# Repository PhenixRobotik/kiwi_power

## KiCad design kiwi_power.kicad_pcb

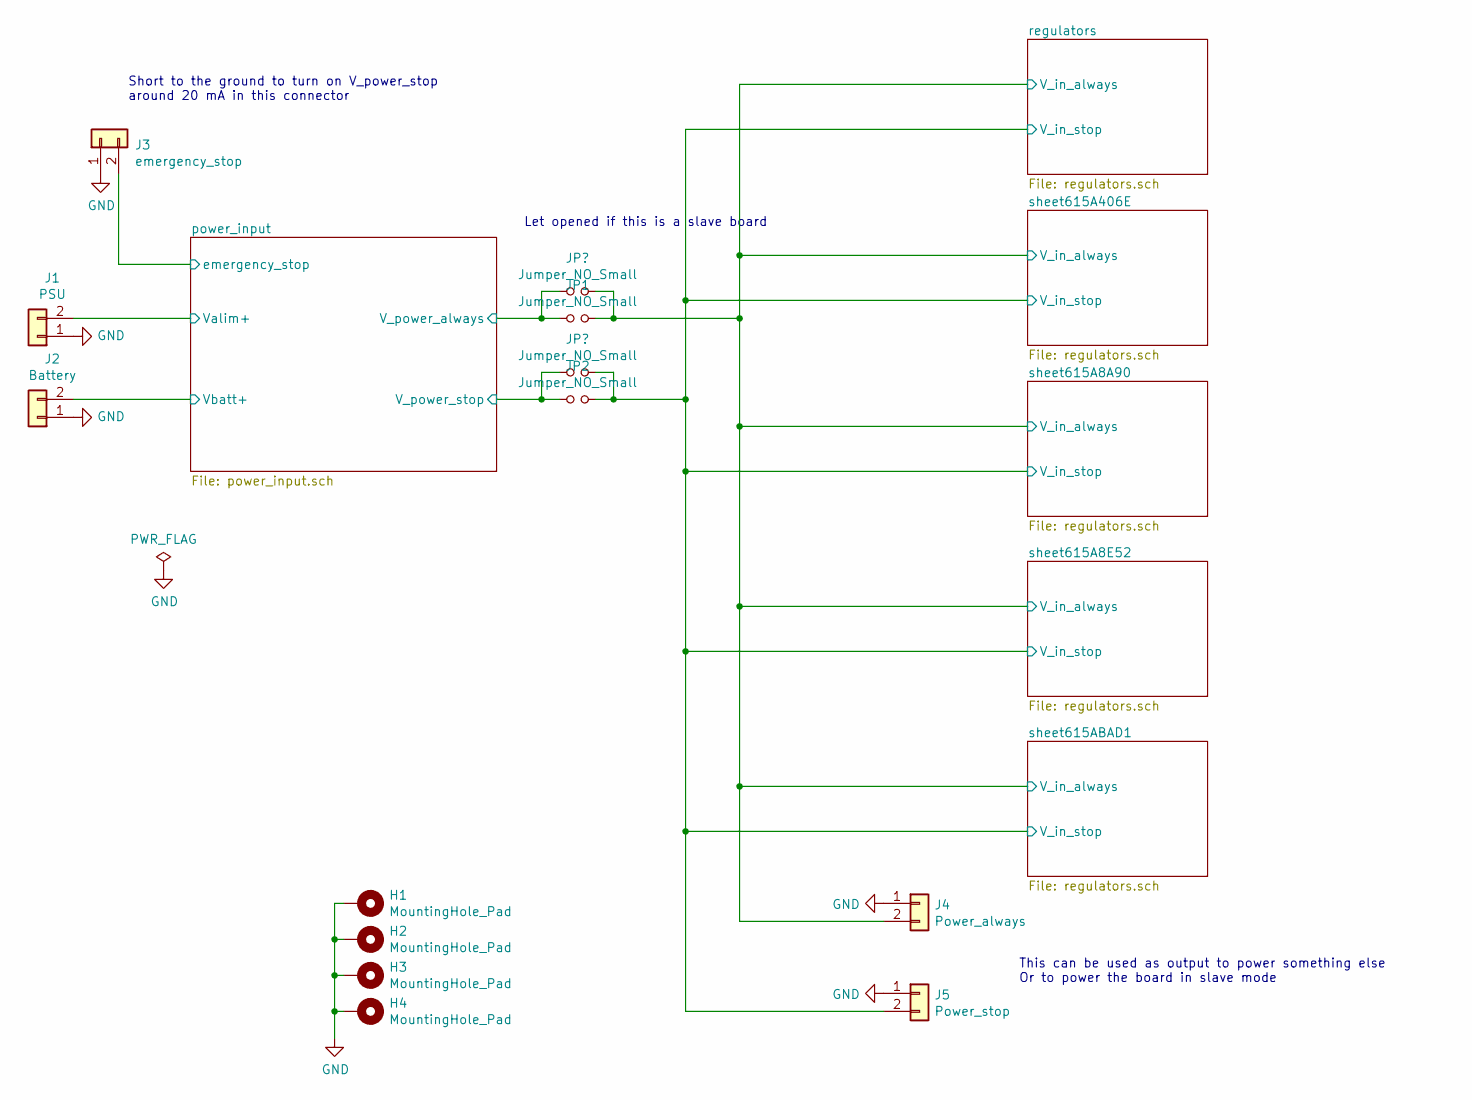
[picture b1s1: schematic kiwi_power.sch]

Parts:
H1, H2, H3, H4: MountingHole_Pad; MountingHole_3.2mm_M3_DIN965_Pad
J1: PSU; PhoenixContact_MSTBA_2,5_2-G-5,08_1x02_P5.08mm_Horizontal
J2: Battery; PhoenixContact_MSTBA_2,5_2-G-5,08_1x02_P5.08mm_Horizontal
J3: emergency_stop; JST_PH_S2B-PH-K_1x02_P2.00mm_Horizontal
J4: Power_always; PhoenixContact_MC_1,5_2-G-3.81_1x02_P3.81mm_Horizontal
J5: Power_stop; PhoenixContact_MC_1,5_2-G-3.81_1x02_P3.81mm_Horizontal
JP1, JP2: Jumper_NO_Small; PinHeader_1x02_P2.54mm_Vertical

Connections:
/power_input/V_power_always: JP1.1; also elsewhere on the board
/power_input/V_power_stop: JP2.1; also elsewhere on the board
/power_input/Valim+: J1.2; also elsewhere on the board
/power_input/Vbatt+: J2.2; also elsewhere on the board
/power_input/emergency_stop: J3.2; also elsewhere on the board
/regulators/V_in_always: J4.2, JP1.2; also elsewhere on the board
/regulators/V_in_stop: J5.2, JP2.2; also elsewhere on the board
GND: H1.1, H2.1, H3.1, H4.1, J1.1, J2.1, J3.1, J4.1, J5.1; also elsewhere on the board

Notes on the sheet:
Short to the ground to turn on V_power_stop around 20 mA in this connector
Let opened if this is a slave board
This can be used as output to power something else Or to power the board in slave mode

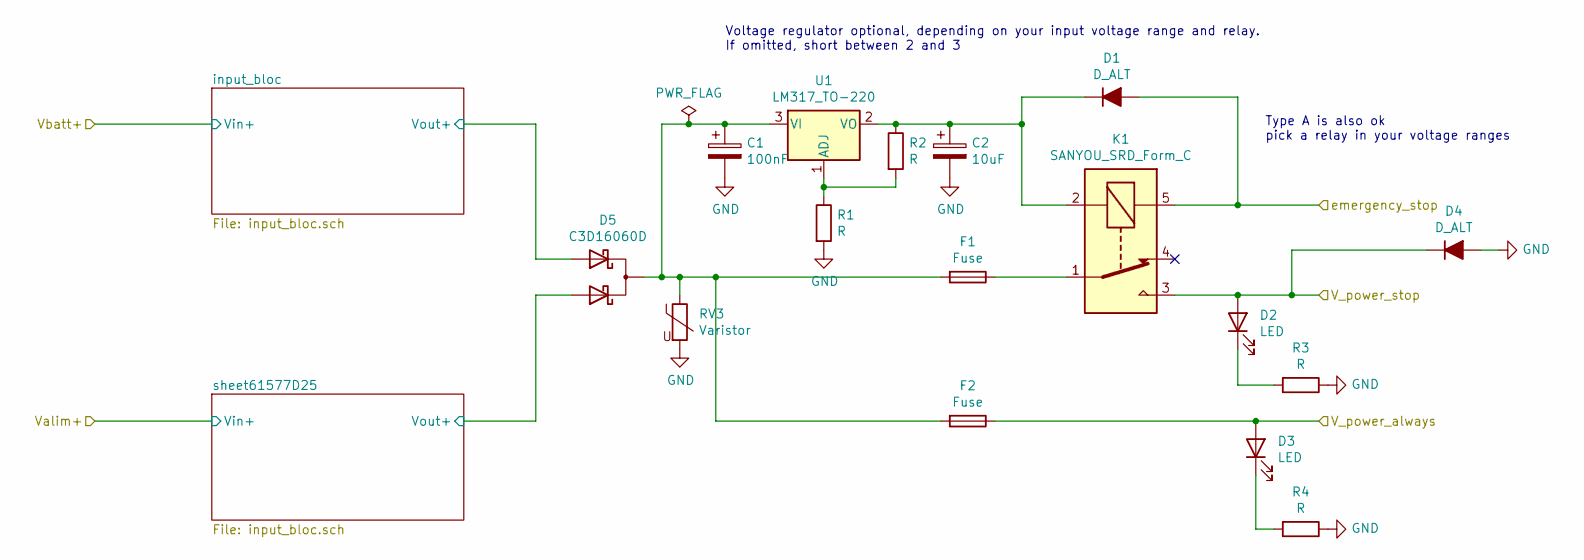
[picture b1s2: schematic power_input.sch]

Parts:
C1: 100nF; CP_Radial_D5.0mm_P2.00mm
C2: 10uF; CP_Radial_D5.0mm_P2.00mm
D1, D4: D_ALT; D_DO-35_SOD27_P10.16mm_Horizontal
D2, D3: LED; LED_D5.0mm
D5: C3D16060D; TO-220-3_Vertical
F1, F2: Fuse; Fuse_Littelfuse_372_D8.50mm
K1: SANYOU_SRD_Form_C; Relay_SPDT_SANYOU_SRD_Series_Form_C
R1, R2, R3, R4: R; R_Axial_DIN0207_L6.3mm_D2.5mm_P10.16mm_Horizontal
RV3: Varistor; RV_Disc_D7mm_W4mm_P5mm
U1: LM317_TO-220; TO-220-3_Vertical

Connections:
/power_input/V_power_always: D3.2 (A), F2.1; also elsewhere on the board
/power_input/V_power_stop: D2.2 (A), D4.1 (K), K1.3; also elsewhere on the board
/power_input/emergency_stop: D1.2 (A), K1.5; also elsewhere on the board
/power_input/input_bloc/Vout+: D5.1 (A1); also elsewhere on the board
/power_input/sheet61577D25/Vout+: D5.3 (A2); also elsewhere on the board
GND: C1.2, C2.2, D4.2 (A), R1.2, R3.1, R4.1, RV3.2; also elsewhere on the board
unnamed: C1.1, D5.2 (K), F1.2, F2.2, RV3.1, U1.3 (VI)
unnamed: C2.1, D1.1 (K), K1.2, R2.1, U1.2 (VO)
unnamed: D2.1 (K), R3.2
unnamed: D3.1 (K), R4.2
unnamed: F1.1, K1.1
unnamed: R1.1, R2.2, U1.1 (ADJ)

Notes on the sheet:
Type A is also ok pick a relay in your voltage ranges
Voltage regulator optional, depending on your input voltage range and relay. If omitted, short between 2 and 3

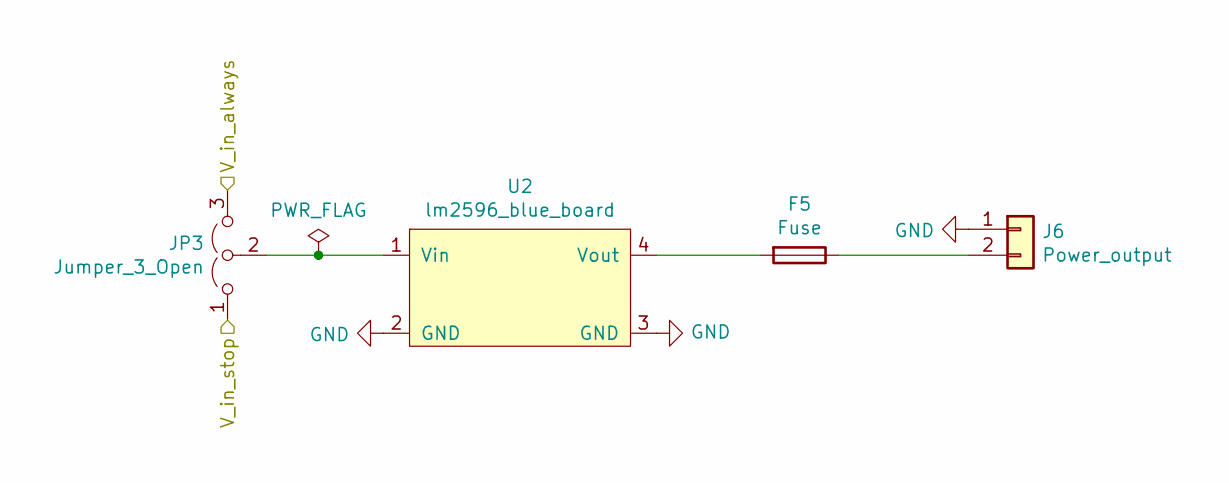
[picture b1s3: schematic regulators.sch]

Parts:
F5: Fuse; Fuse_Littelfuse_372_D8.50mm
J6: Power_output; PhoenixContact_MC_1,5_2-G-3.81_1x02_P3.81mm_Horizontal
JP3: Jumper_3_Open; PinHeader_1x03_P2.54mm_Vertical
U2: lm2596_blue_board

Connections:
/regulators/V_in_always: JP3.3 (B); also elsewhere on the board
/regulators/V_in_stop: JP3.1 (A); also elsewhere on the board
GND: J6.1, U2.2 (GND), U2.3 (GND); also elsewhere on the board
unnamed: F5.1, J6.2
unnamed: F5.2, U2.4 (Vout)
unnamed: JP3.2 (C), U2.1 (Vin)

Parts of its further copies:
F6, F7, F8, F9: Fuse; Fuse_Littelfuse_372_D8.50mm
J7, J8, J9, J10: Power_output; PhoenixContact_MC_1,5_2-G-3.81_1x02_P3.81mm_Horizontal
JP4, JP5, JP6, JP7: Jumper_3_Open; PinHeader_1x03_P2.54mm_Vertical
U3, U4, U5, U6: lm2596_blue_board

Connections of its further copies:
/regulators/V_in_always: JP4.3 (B), JP5.3 (B), JP6.3 (B), JP7.3 (B); also elsewhere on the board
/regulators/V_in_stop: JP4.1 (A), JP5.1 (A), JP6.1 (A), JP7.1 (A); also elsewhere on the board
GND: J7.1, J8.1, J9.1, J10.1, U3.2 (GND), U3.3 (GND), U4.2 (GND), U4.3 (GND), U5.2 (GND), U5.3 (GND), U6.2 (GND), U6.3 (GND); also elsewhere on the board
unnamed: F6.1, J7.2
unnamed: F6.2, U3.4 (Vout)
unnamed: F7.1, J8.2
unnamed: F7.2, U4.4 (Vout)
unnamed: F8.1, J9.2
unnamed: F8.2, U5.4 (Vout)
unnamed: F9.1, J10.2
unnamed: F9.2, U6.4 (Vout)
unnamed: JP4.2 (C), U3.1 (Vin)
unnamed: JP5.2 (C), U4.1 (Vin)
unnamed: JP6.2 (C), U5.1 (Vin)
unnamed: JP7.2 (C), U6.1 (Vin)

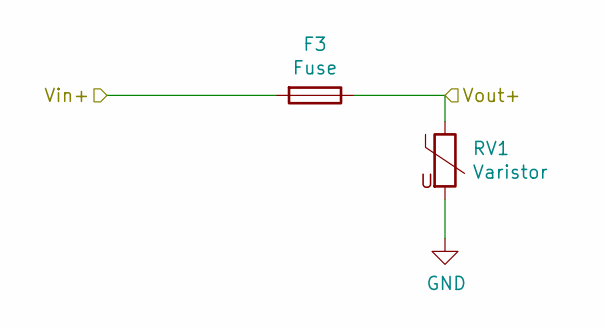
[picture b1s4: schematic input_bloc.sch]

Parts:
F3: Fuse; Fuse_Littelfuse_372_D8.50mm
RV1: Varistor; RV_Disc_D7mm_W4mm_P5mm

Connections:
/power_input/Vbatt+: F3.2; also elsewhere on the board
/power_input/input_bloc/Vout+: F3.1, RV1.1; also elsewhere on the board
GND: RV1.2; also elsewhere on the board

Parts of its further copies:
F4: Fuse; Fuse_Littelfuse_372_D8.50mm
RV2: Varistor; RV_Disc_D7mm_W4mm_P5mm

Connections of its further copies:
/power_input/Valim+: F4.2; also elsewhere on the board
/power_input/sheet61577D25/Vout+: F4.1, RV2.1; also elsewhere on the board
GND: RV2.2; also elsewhere on the board

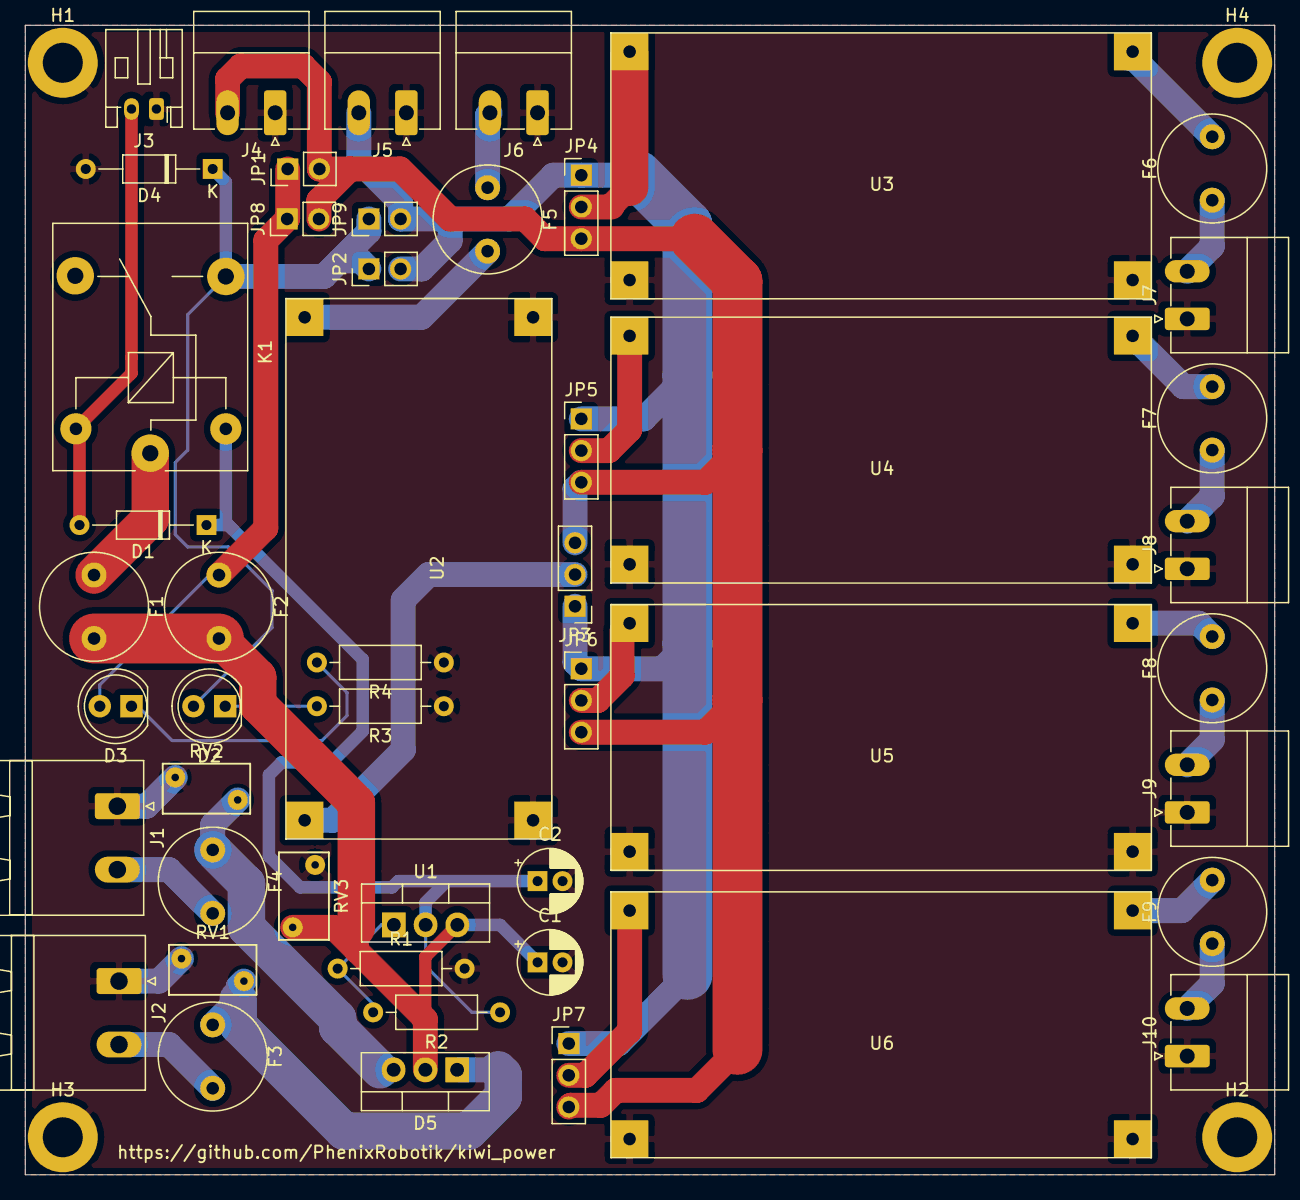
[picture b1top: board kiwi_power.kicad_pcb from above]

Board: 2 copper layers, 100.0 x 92.0 mm, 53 parts (0 on the bottom side), 31 nets.

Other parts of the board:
JP8, JP9: Jumper_NO_Small; PinHeader_1x02_P2.54mm_Vertical

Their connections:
/power_input/V_power_always: JP8.1; also elsewhere on the board
/power_input/V_power_stop: JP9.1; also elsewhere on the board
/regulators/V_in_always: JP8.2; also elsewhere on the board
/regulators/V_in_stop: JP9.2; also elsewhere on the board

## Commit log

2021-10-02 first version
2021-10-02 fixing wrong diode symbol for simulation only
2021-10-09 added link and logo
2021-11-07 version 2
